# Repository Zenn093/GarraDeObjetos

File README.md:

# GarraDeObjetos
Es un proyecto el cual reutiliza el sistema de una impresora 3D, aprovechando la movilidad dle eje en X Y.

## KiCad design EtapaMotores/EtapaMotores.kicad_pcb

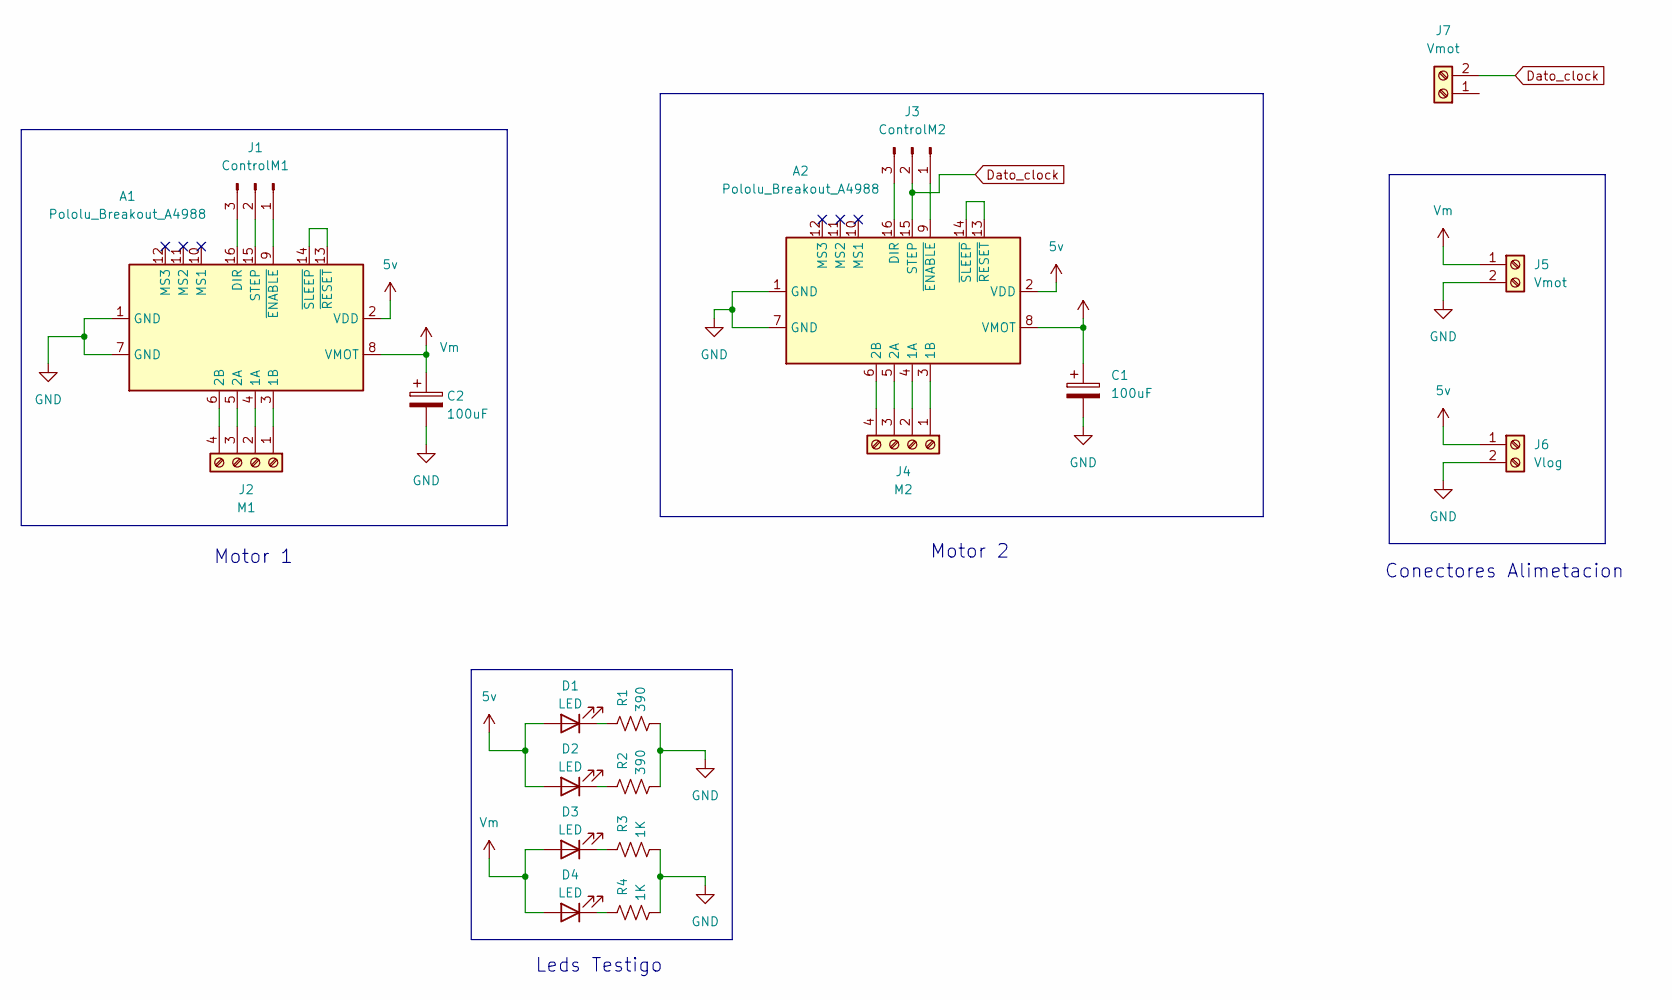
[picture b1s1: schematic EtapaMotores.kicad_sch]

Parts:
A1, A2: Pololu_Breakout_A4988; Pololu_Breakout-16_15.2x20.3mm
C1, C2: 100uF; CP_Radial_D8.0mm_P3.50mm
D1, D2, D3, D4: LED; LED_D1.8mm_W3.3mm_H2.4mm
J1: ControlM1; PinHeader_1x03_P2.54mm_Vertical
J2: M1; TerminalBlock_Phoenix_MKDS-1,5-4-5.08_1x04_P5.08mm_Horizont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
J3: ControlM2; PinHeader_1x03_P2.54mm_Vertical
J4: M2; TerminalBlock_Phoenix_MKDS-1,5-4-5.08_1x04_P5.08mm_Horizont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
J5, J7: Vmot; TerminalBlock_Phoenix_MKDS-1,5-2-5.08_1x02_P5.08mm_Horizont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
J6: Vlog; TerminalBlock_Phoenix_MKDS-1,5-2-5.08_1x02_P5.08mm_Horizont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
R1, R2: 390; R_Axial_DIN0207_L6.3mm_D2.5mm_P10.16mm_Horizontal
R3, R4: 1K; R_Axial_DIN0207_L6.3mm_D2.5mm_P10.16mm_Horizontal

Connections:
5v: A1.2 (VDD), A2.2 (VDD), D1.2 (A), D2.2 (A), J6.1
Dato_clock: A2.15 (STEP), J3.2, J7.2
GND: A1.1 (GND), A1.7 (GND), A2.1 (GND), A2.7 (GND), C1.2, C2.2, J5.2, J6.2, R1.2, R2.2, R3.2, R4.2
unnamed: A1.4 (1A), J2.2
unnamed: A1.3 (1B), J2.1
unnamed: A1.5 (2A), J2.3
unnamed: A1.6 (2B), J2.4
unnamed: A1.16 (DIR), J1.3
unnamed: A1.15 (STEP), J1.2
unnamed: A1.9 (~ENABLE), J1.1
unnamed: A1.13 (~RESET), A1.14 (~SLEEP)
unnamed: A2.4 (1A), J4.2
unnamed: A2.3 (1B), J4.1
unnamed: A2.5 (2A), J4.3
unnamed: A2.6 (2B), J4.4
unnamed: A2.16 (DIR), J3.3
unnamed: A2.9 (~ENABLE), J3.1
unnamed: A2.13 (~RESET), A2.14 (~SLEEP)
unnamed: D1.1 (K), R1.1
unnamed: D2.1 (K), R2.1
unnamed: D3.1 (K), R3.1
unnamed: D4.1 (K), R4.1
Vm: A1.8 (VMOT), A2.8 (VMOT), C1.1, C2.1, D3.2 (A), D4.2 (A), J5.1

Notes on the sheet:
Leds Testigo
Conectores Alimetacion
Motor 1
Motor 2

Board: 2 copper layers, 18 parts (0 on the bottom side), 23 nets, no tracks yet.
